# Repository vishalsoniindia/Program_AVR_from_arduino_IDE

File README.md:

# Program_AVR_from_arduino_IDE
In this tutorial you can upload program in any AVR controller from arduino IDE. you can also upload hex file in any AVR.
you can find arduino pinout for AVR controllers list given below.
Attiny25/45/85
Attiny24/44/84
Atmega8/48/88/168/328
Atmega8535/16/32

_________________________________________________

Youtube :- https://youtu.be/DxuucFgY1B4

_________________________________________________

instructables :- https://www.instructables.com/How-to-Program-Any-Type-of-AVR-Microcontroller-Wit/

________________________________________________

hackster :- https://www.hackster.io/Vishalsoniindia/how-to-program-any-type-of-avr-microcontroller-with-arduino-28b644

________________________________________________

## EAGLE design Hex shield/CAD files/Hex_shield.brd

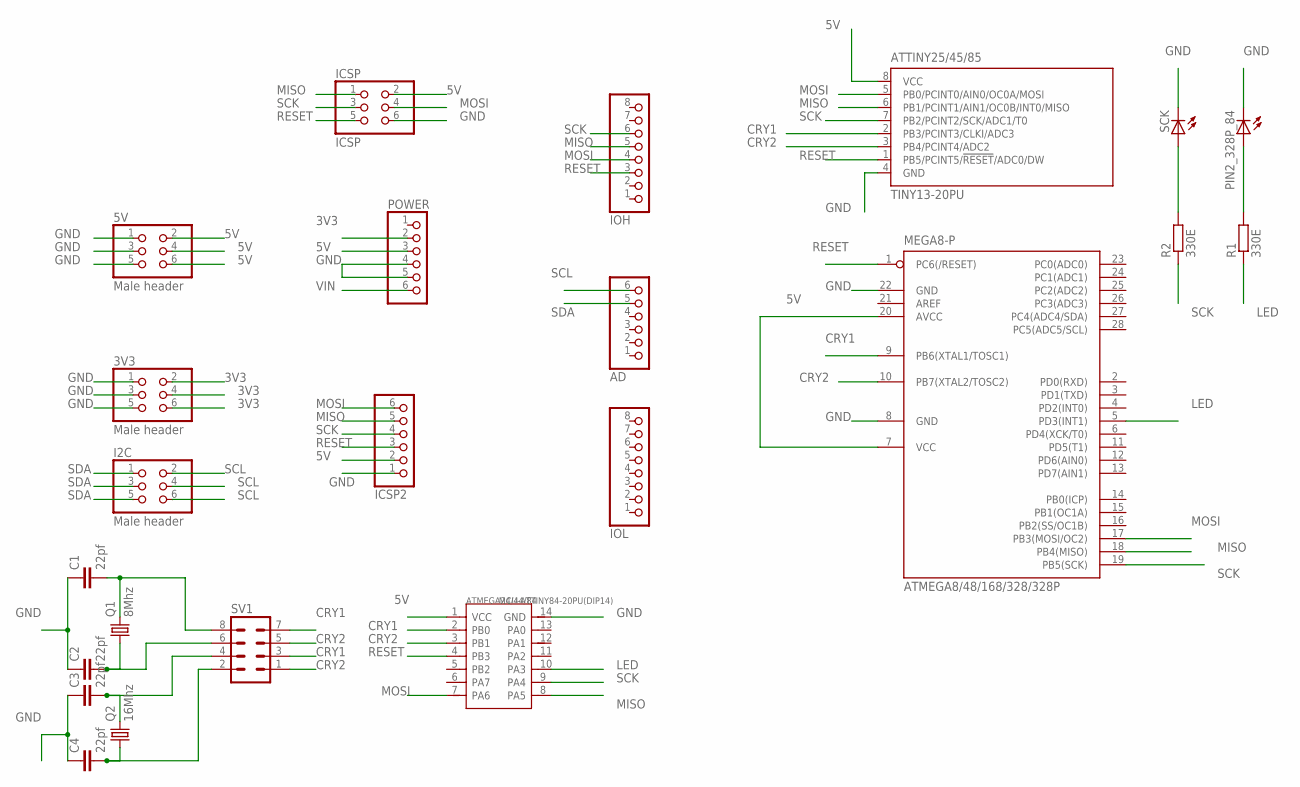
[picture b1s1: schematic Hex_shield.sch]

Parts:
3V3, 5V: Male header; 2X03
AD: PINHD-1X6; 1X06
ATMEGA8/48/168/328/328P: MEGA8-P; DIL28-3
ATMEGA24/44/84: MCU-ATTINY84-20PU(DIP14); DIP14-2.54-17.24X6.35MM
ATTINY25/45/85: TINY13-20PU; DIL08
C1, C2, C3, C4: 22pf; C2.5-2
I2C: Male header; 2X03
ICSP: ICSP; 2X03
ICSP2: PINHD-1X6; 1X06
IOH: PINHD-1X8; 1X08
IOL: PINHD-1X8; 1X08
PIN2_328P_84: LED5MM
POWER: PINHD-1X6; 1X06
Q1: 8Mhz; HC49/S
Q2: 16Mhz; HC49/S
R1, R2: 330E; 0204/7
SCK: LED5MM
SV1: MA04-2

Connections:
3V3: 3V3.2, 3V3.4, 3V3.6, POWER.2
5V: 5V.2, 5V.4, 5V.6, ATMEGA8/48/168/328/328P.7 (VCC), ATMEGA8/48/168/328/328P.20 (AVCC), ATMEGA24/44/84.1 (VCC), ATTINY25/45/85.8 (VCC), ICSP.2, ICSP2.2, POWER.3
CRY1: ATMEGA8/48/168/328/328P.9 (PB6(XTAL1/TOSC1)), ATMEGA24/44/84.2 (PB0), ATTINY25/45/85.2 (PB3/PCINT3/CLKI/ADC3), SV1.3, SV1.7
CRY2: ATMEGA8/48/168/328/328P.10 (PB7(XTAL2/TOSC2)), ATMEGA24/44/84.3 (PB1), ATTINY25/45/85.3 (PB4/PCINT4/ADC2), SV1.1, SV1.5
GND: 3V3.1, 3V3.3, 3V3.5, 5V.1, 5V.3, 5V.5, ATMEGA8/48/168/328/328P.8 (GND), ATMEGA8/48/168/328/328P.22 (GND), ATMEGA24/44/84.14 (GND), ATTINY25/45/85.4 (GND), C1.1, C2.1, C3.1, C4.1, ICSP.6, ICSP2.1, PIN2_328P_84.K (C), POWER.4, POWER.5, SCK.K (C)
LED: ATMEGA8/48/168/328/328P.5 (PD3(INT1)), ATMEGA24/44/84.10 (PA3), R1.1
MISO: ATMEGA8/48/168/328/328P.18 (PB4(MISO)), ATMEGA24/44/84.8 (PA5), ATTINY25/45/85.6 (PB1/PCINT1/AIN1/OC0B/INT0/MISO), ICSP.1, ICSP2.5, IOH.5
MOSI: ATMEGA8/48/168/328/328P.17 (PB3(MOSI/OC2)), ATMEGA24/44/84.7 (PA6), ATTINY25/45/85.5 (PB0/PCINT0/AIN0/OC0A/MOSI), ICSP.4, ICSP2.6, IOH.4
unnamed: C3.2, Q2.2, SV1.4
unnamed: C4.2, Q2.1, SV1.2
unnamed: R2.2, SCK.A
unnamed: PIN2_328P_84.A, R1.2
unnamed: C1.2, Q1.2, SV1.8
unnamed: C2.2, Q1.1, SV1.6
RESET: ATMEGA8/48/168/328/328P.1 (PC6(/RESET)), ATMEGA24/44/84.4 (PB3), ATTINY25/45/85.1 (PB5/PCINT5/!RESET!/ADC0/DW), ICSP.5, ICSP2.3, IOH.3
SCK: ATMEGA8/48/168/328/328P.19 (PB5(SCK)), ATMEGA24/44/84.9 (PA4), ATTINY25/45/85.7 (PB2/PCINT2/SCK/ADC1/T0), ICSP.3, ICSP2.4, IOH.6, R2.1
SCL: AD.6, I2C.2, I2C.4, I2C.6
SDA: AD.5, I2C.1, I2C.3, I2C.5
VIN: POWER.6

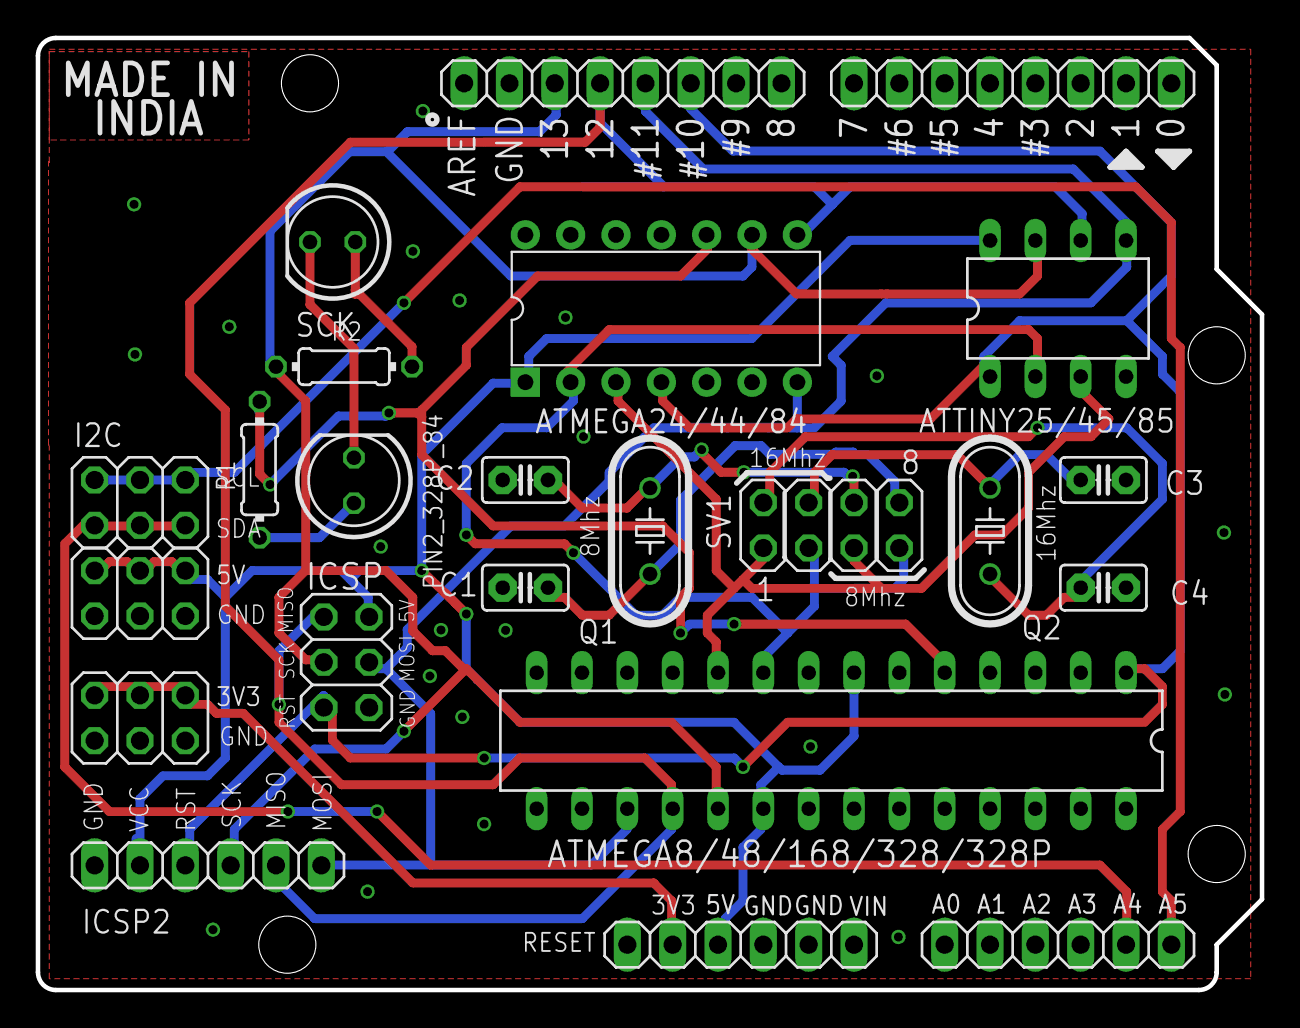
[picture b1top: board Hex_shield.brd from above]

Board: 2 copper layers, 68.6 x 53.3 mm, 23 parts (0 on the bottom side), 18 nets.

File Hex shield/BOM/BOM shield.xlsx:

Qty | Value | Device | Package | Parts | Description
2.0 | LED | LED5MM | LED5MM | PIN2_328P_84, SCK | LED
1.0 | 16Mhz | CRYSTALHC49S | HC49/S | Q2 | CRYSTAL
4.0 | 22pf | C2.5/2 | C2.5-2 | C1, C2, C3, C4 | CAPACITOR
2.0 | 330E | R0204/7 | 0204/7 | R1, R2 | RESISTOR, European symbol
1.0 | 8Mhz | CRYSTALHC49S | HC49/S | Q1 | CRYSTAL
1.0 | (DIP14) | ATTINY84 | DIP14-2.54-17.24X6.35MM | ATMEGA24/44/84 | 310010126 Check prices
1.0 | MEGA8-P | MEGA8-P | DIL28-3 | ATMEGA8/48/168/328/328P | MICROCONTROLLER
1.0 | (DIP8) | TINY13-20PU | DIL08 | ATTINY25/45/85 | 8-bit AVR Microcontroller with 1K Bytes In-System Programmable Flash
